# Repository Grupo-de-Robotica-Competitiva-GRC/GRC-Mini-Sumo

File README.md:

# GRC-Mini-Sumo

## Descrição

O presente projeto se trata de um robô de competições de sumo, da modalidade de mini sumo autônomo. O robô utiliza sensores para detecção de oponentes e se dispoê de uma lógica de combate para empurrar o adversário para fora da arena, tudo isso enquanto evita, por si próprio, sair da arena. O projeto engloba eletrônica, embarcados, desenvolvimento de firmware, modelagem de controle e modelagem 3D.

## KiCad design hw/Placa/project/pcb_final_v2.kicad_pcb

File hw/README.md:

# HARDWARE

Ficheiro referente a todo material relacionado a Hardware

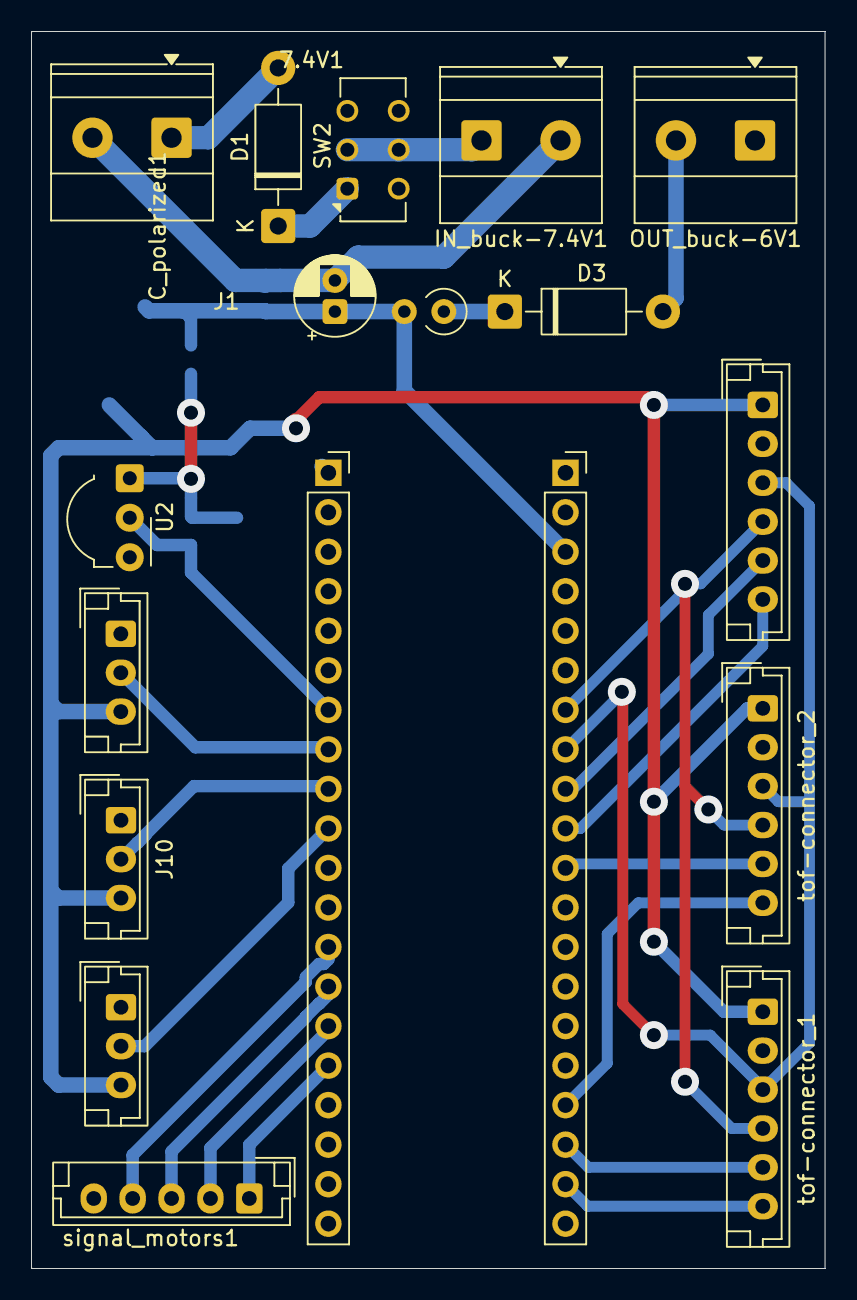
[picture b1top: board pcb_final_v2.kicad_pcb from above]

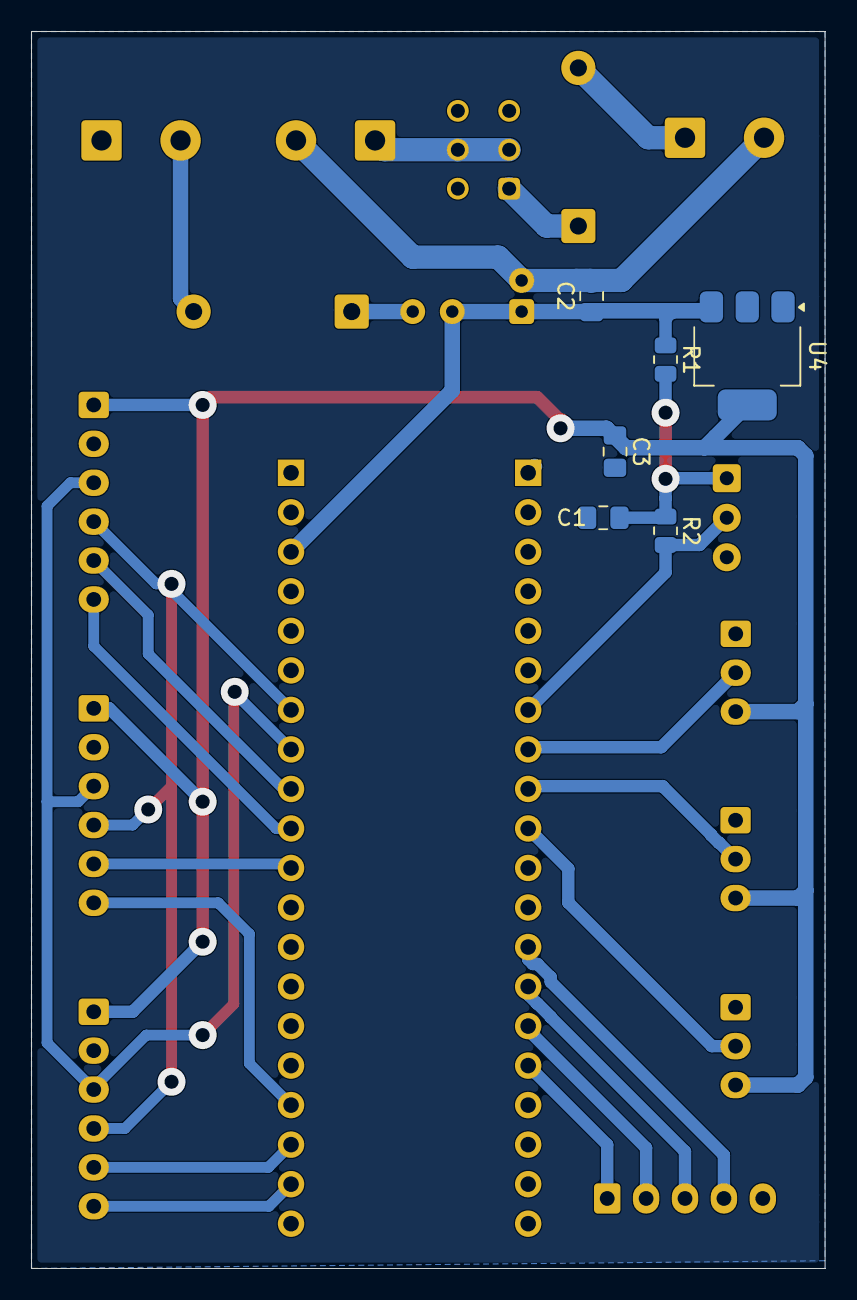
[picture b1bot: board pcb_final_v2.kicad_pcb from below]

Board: 2 copper layers, 51.0 x 79.5 mm, 24 parts (6 on the bottom side), 26 nets.

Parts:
7.4V1: KRE borne; TerminalBlock_Phoenix_MKDS-1,5-2-5.08_1x02_P5.08mm_Horizont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
C1: 4,7uF; C_0805_2012Metric_Pad1.18x1.45mm_HandSolder
C2, C3: 100nF; C_0805_2012Metric_Pad1.18x1.45mm_HandSolder
C_polarized1: 100uH; CP_Radial_D5.0mm_P2.00mm
D1, D3: D; D_DO-41_SOD81_P10.16mm_Horizontal
IN_buck-7.4V1: KRE borne; TerminalBlock_Phoenix_MKDS-1,5-2-5.08_1x02_P5.08mm_Horizont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
J1, J2: pin_socket-bluepill; PinSocket_1x20_P2.54mm_Vertical
J9: tof-connector_3; JST_EH_B6B-EH-A_1x06_P2.50mm_Vertical
J10: tcrt5000_conector_2; JST_EH_B3B-EH-A_1x03_P2.50mm_Vertical
J11: tcrt5000_conector_3; JST_EH_B3B-EH-A_1x03_P2.50mm_Vertical
J12: tcrt5000_conector_1; JST_EH_B3B-EH-A_1x03_P2.50mm_Vertical
L1: 100uH; L_Axial_L6.6mm_D2.7mm_P2.54mm_Vertical_Vishay_IM-2
OUT_buck-6V1: KRE borne; TerminalBlock_Phoenix_MKDS-1,5-2-5.08_1x02_P5.08mm_Horizont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
R1: 330 ohm; R_0805_2012Metric
R2: 10k ohm; R_0805_2012Metric
SW2: key; SW_CK_JS202011CQN_DPDT_Straight
U2: Receptor IR; Vishay_MOLD-3Pin
U4: AMS1117-3.3; SOT-223-3_TabPin2
signal_motors1: jst connector; JST_EH_B5B-EH-A_1x05_P2.50mm_Vertical
tof-connector_1, tof-connector_2: JST_EH_B6B-EH-A_1x06_P2.50mm_Vertical

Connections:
+3V3: C3.1, J9.1, J10.3, J11.3, J12.3, U4.2 (VO), tof-connector_1.1, tof-connector_2.1
+5V: C2.1, C_polarized1.1, J2.3, L1.2, R1.1, U4.3 (VI)
+7.4V: IN_buck-7.4V1.1, SW2.2 (B)
D1: J1.7, R2.2, U2.1 (OUT)
D2: J1.8, J12.2
D3: J1.9, J10.2
D4: J1.10, J11.2
GNDPWR: 7.4V1.1, C2.2, C_polarized1.2, IN_buck-7.4V1.2, U4.1 (GND)
GNDS: C1.2, C3.2, J1.1, J2.2, J9.2, J10.1, J11.1, J12.1, OUT_buck-6V1.1, U2.3 (GND), signal_motors1.5, tof-connector_1.2, tof-connector_2.2
GPIO1: J2.18, tof-connector_1.5
GPIO2: J2.11, tof-connector_2.5
GPIO3: J2.9, J9.5
I2C1_SCL: J2.8, J9.3, tof-connector_1.3, tof-connector_2.3
I2C1_SDA: J2.7, J9.4, tof-connector_1.4, tof-connector_2.4
MA+: J1.16, signal_motors1.1
MA-: J1.15, signal_motors1.2
MB+: J1.14, signal_motors1.3
MB-: J1.13, signal_motors1.4
unnamed: 7.4V1.2, D1.2 (A)
unnamed: D1.1 (K), SW2.1 (A)
unnamed: D3.2 (A), OUT_buck-6V1.2
unnamed: D3.1 (K), L1.1
unnamed: C1.1, R1.2, R2.1, U2.2 (Vs)
XSHUT1: J2.19, tof-connector_1.6
XSHUT2: J2.17, tof-connector_2.6
XSHUT3: J2.10, J9.6

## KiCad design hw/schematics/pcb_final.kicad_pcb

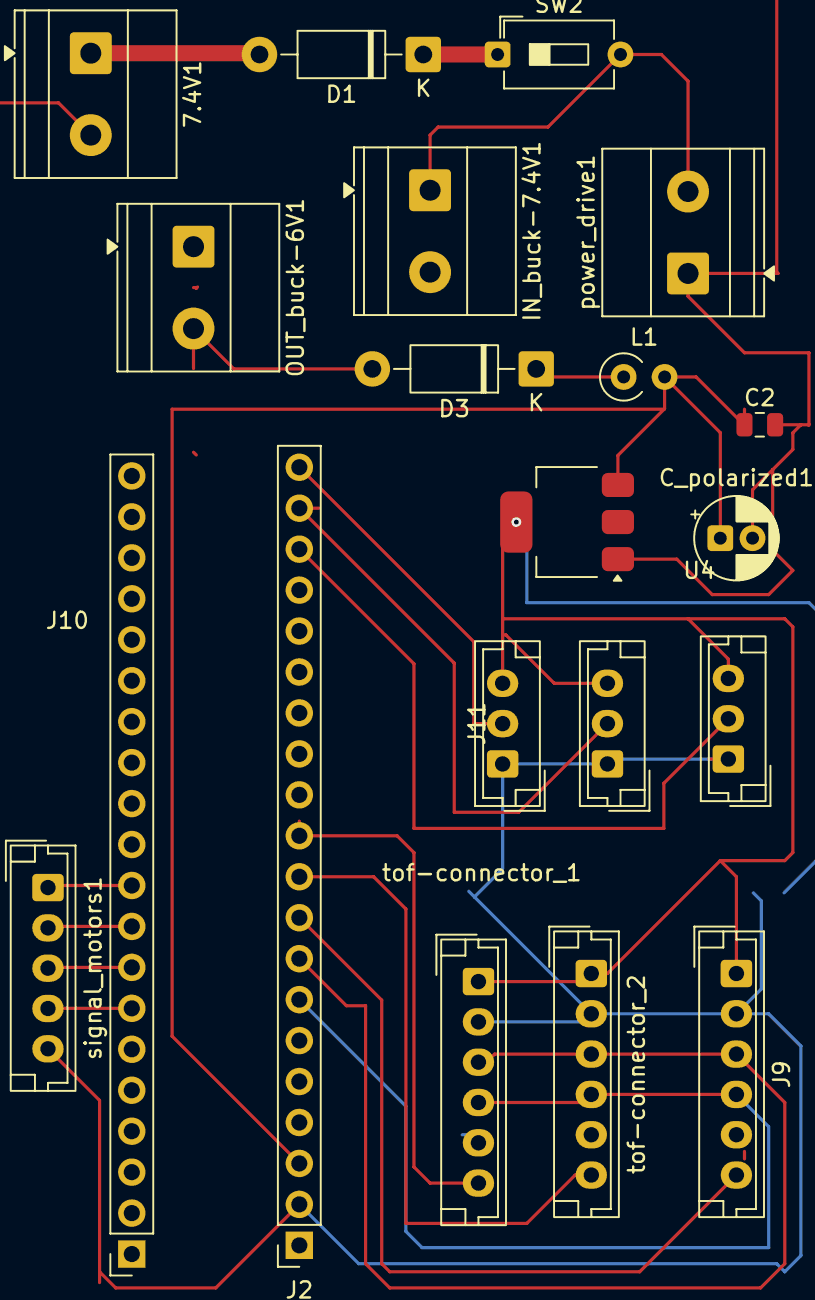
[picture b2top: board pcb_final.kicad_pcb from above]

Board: 2 copper layers, 21 parts (1 on the bottom side), 20 nets.

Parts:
7.4V1: KRE borne; TerminalBlock_Phoenix_MKDS-1,5-2-5.08_1x02_P5.08mm_Horizont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
C2, C3: 100nF; C_0805_2012Metric
C_polarized1: 100uH; CP_Radial_D5.0mm_P2.00mm
D1, D3: D; D_DO-41_SOD81_P10.16mm_Horizontal
IN_buck-7.4V1: KRE borne; TerminalBlock_Phoenix_MKDS-1,5-2-5.08_1x02_P5.08mm_Horizont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
J1, J2: pin_socket-bluepill; PinSocket_1x20_P2.54mm_Vertical
J9: tof-connector_3; JST_EH_B6B-EH-A_1x06_P2.50mm_Vertical
J10: tcrt5000_conector_2; JST_EH_B3B-EH-A_1x03_P2.50mm_Vertical
J11: tcrt5000_conector_3; JST_EH_B3B-EH-A_1x03_P2.50mm_Vertical
J12: tcrt5000_conector_1; JST_EH_B3B-EH-A_1x03_P2.50mm_Vertical
L1: 100uH; L_Axial_L6.6mm_D2.7mm_P2.54mm_Vertical_Vishay_IM-2
OUT_buck-6V1: KRE borne; TerminalBlock_Phoenix_MKDS-1,5-2-5.08_1x02_P5.08mm_Horizont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
SW2: key; SW_DIP_SPSTx01_Slide_6.7x4.1mm_W7.62mm_P2.54mm_LowProfile
U4: AMS1117-3.3; SOT-223-3_TabPin2
power_drive1: KRE borne; TerminalBlock_Phoenix_MKDS-1,5-2-5.08_1x02_P5.08mm_Horizont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
signal_motors1: jst connector; JST_EH_B5B-EH-A_1x05_P2.50mm_Vertical
tof-connector_1, tof-connector_2: JST_EH_B6B-EH-A_1x06_P2.50mm_Vertical

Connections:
+3V3: C3.1, J9.1, J10.3, J11.3, J12.3, U4.2 (VO), tof-connector_1.1, tof-connector_2.1
+5V: C2.1, C_polarized1.1, J2.3, L1.2, U4.3 (VI)
D1: J2.18, J12.2
D2: J2.19, J10.2
D3: J2.20, J11.2
GNDPWR: 7.4V1.1, 7.4V1.2, C2.2, C_polarized1.2, D1.2 (A), SW2.2 (B), U4.1 (GND), power_drive1.1, power_drive1.2
GNDS: C3.2, J2.2, J9.2, J10.1, J11.1, J12.1, signal_motors1.5, tof-connector_1.2, tof-connector_2.2
I2C1_SCL: J2.8, J9.3, tof-connector_1.3, tof-connector_2.3
I2C1_SDA: J2.7, J9.4, tof-connector_1.4, tof-connector_2.4
MA+: J1.10, signal_motors1.1
MA-: J1.9, signal_motors1.2
MB+: J1.8, signal_motors1.3
MB-: J1.7, signal_motors1.4
unnamed: D1.1 (K), SW2.1 (A)
unnamed: D3.2 (A), OUT_buck-6V1.2
unnamed: D3.1 (K), L1.1
unnamed: IN_buck-7.4V1.1 (Pin_1_1), OUT_buck-6V1.1
XSHUT1: J2.11, tof-connector_1.6
XSHUT2: J2.10, tof-connector_2.6
XSHUT3: J2.9, J9.6

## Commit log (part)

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2026-05-07 Correct project name in README
2026-05-07 Divisão e organização de ficheiros do repositorio
2026-05-07 Add initial README for firmware documentation
2026-05-07 Add README.md for hardware documentation
2026-05-07 Add initial README with project resources
2026-05-11 Update README with project description
    Added project description for GRC-Mini-Sumo.
2026-05-12 Create schematics
2026-05-12 Create kicad
2026-05-13 Teste inicial com sensor de distancia
2026-05-15 add teste pwm
2026-05-17 Update README.md with PWM test objective
    Add objectives and timer pre-scaler definition for PWM test.
2026-05-17 finalização da descrição do teste de pwm
2026-05-17 ajustes no codigo do pwmteste
2026-05-18 Correcao do sensor VL53LX0 (Funcionando corretamente)
2026-05-19 Adicionando comentários ao código
2026-05-20 Adicionando documentação
2026-05-20 mudança nos pinos de pwm e atulização da documentação
2026-05-20 ateracoes na documentacao pwm
2026-05-21 Esquematíco inicial da alimentação
2026-05-21 mover esquema dos sensores para Schematics
2026-05-21 deletar esquemáticos inválidos
2026-05-21 Revert "deletar esquemáticos inválidos"
    This reverts commit e4951a43d0abfea7f3b07e9c38223771aa14c0d2.
2026-05-21 Revert "mover esquema dos sensores para Schematics"
    This reverts commit 5228f44a55bb4b5e3b4e1790ade132ec4117c8b8.
2026-05-21 retirando esq. de sensores da main
2026-05-24 Esquematico dos motores
2026-05-24 Esquematicos M
2026-06-11 correcoes no codigo pwm
2026-06-11 correcao na frequencia do pwm
